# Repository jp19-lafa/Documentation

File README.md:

[![Contributors][contributors-shield]][contributors-url]
[![Forks][forks-shield]][forks-url]
[![Stargazers][stars-shield]][stars-url]
[![Issues][issues-shield]][issues-url]
[![MIT License][license-shield]][license-url]

<!-- PROJECT LOGO -->
<br />
<p align="center">

  <h3 align="center">DOCUMENTATION</h3>

  <p align="center">
    Wiki for farmlab
    <br />
    <a href="https://github.com/jp19-lafa/Documentation/wiki"><strong>Explore the docs »</strong></a>
    <br />
    <br />
    <a href="https://github.com/jp19-lafa/Documentation/issues">Report Bug</a>
    ·
    <a href="https://github.com/jp19-lafa/Documentation/issues">Request Feature</a>
  </p>
</p>

<!-- TABLE OF CONTENTS -->
## Table of Contents

- [Table of Contents](#table-of-contents)
- [About The Project](#about-the-project)
- [Roadmap](#roadmap)
- [Contributing](#contributing)
- [License](#license)
- [Team](#team)

<!-- ABOUT THE PROJECT -->
## About The Project
FarmLab is a class project for Smart Systems & IoT 2019 @ AP Antwerp. FarmLab is an automated hydroponics farm that utilizes an array of sensor to make smart decisions an create the optimal growing environment. Multiple nodes can work together to create a big farm network.

The cultivation of these plants follow the 'hydroponics' technique. This means the plants are planted directly in water without any type of soil. They are fed by nutrients added to that water.

_For the full explination please refer to the [Wiki](https://github.com/jp19-lafa/Documentation/wiki)_

<!-- ROADMAP -->
## Roadmap

See the [open issues](https://github.com/jp19-lafa/Documentation/issues) for a list of proposed features (and known issues).

<!-- CONTRIBUTING -->
## Contributing

Contributions are what make the open source community such an amazing place to be learn, inspire, and create. Any contributions you make are **greatly appreciated**.

1. Fork the Project
2. Create your Feature Branch (`git checkout -b feature/AmazingFeature`)
3. Commit your Changes (`git commit -m 'Add some AmazingFeature'`)
4. Push to the Branch (`git push origin feature/AmazingFeature`)
5. Open a Pull Request

<!-- LICENSE -->
## License

Distributed under the MIT License. See `LICENSE` for more information.

<!-- Team -->
## Team

Meurs Michiel - michiel.meurs1@gmail.com
<br>
Meyers Tom - tom@odex.be
<br>
Van Hoof Jonas - Jonas.vanhoof@student.ap.be
<br>
Vinck Ben - <!-- TODO: add a e-mail of Vincks choosing-->
<br>
Willemsen Matthias - <!-- TODO: add a e-mail of Willemsen's choosing-->

Project Link: [https://github.com/jp19-lafa/Documentation](https://github.com/jp19-lafa/Documentation)

<!-- MARKDOWN LINKS & IMAGES -->
<!-- https://www.markdownguide.org/basic-syntax/#reference-style-links -->
[contributors-shield]: https://img.shields.io/github/contributors/jp19-lafa/Documentation.svg?style=flat-square
[contributors-url]: https://github.com/jp19-lafa/Documentation/graphs/contributors
[forks-shield]: https://img.shields.io/github/forks/jp19-lafa/Documentation.svg?style=flat-square
[forks-url]: https://github.com/jp19-lafa/Documentation/network/members
[stars-shield]: https://img.shields.io/github/stars/jp19-lafa/Documentation.svg?style=flat-square
[stars-url]: https://github.com/jp19-lafa/Documentation/stargazers
[issues-shield]: https://img.shields.io/github/issues/jp19-lafa/Documentation.svg?style=flat-square
[issues-url]: https://github.com/jp19-lafa/Documentation/issues
[license-shield]: https://img.shields.io/github/license/jp19-lafa/Documentation.svg?style=flat-square
[license-url]: https://github.com/jp19-lafa/Documentation/blob/master/LICENSE.txt
[product-screenshot]: https://raw.githubusercontent.com/jp19-lafa/Documentation/master/images/branding/plant_transparent.svg

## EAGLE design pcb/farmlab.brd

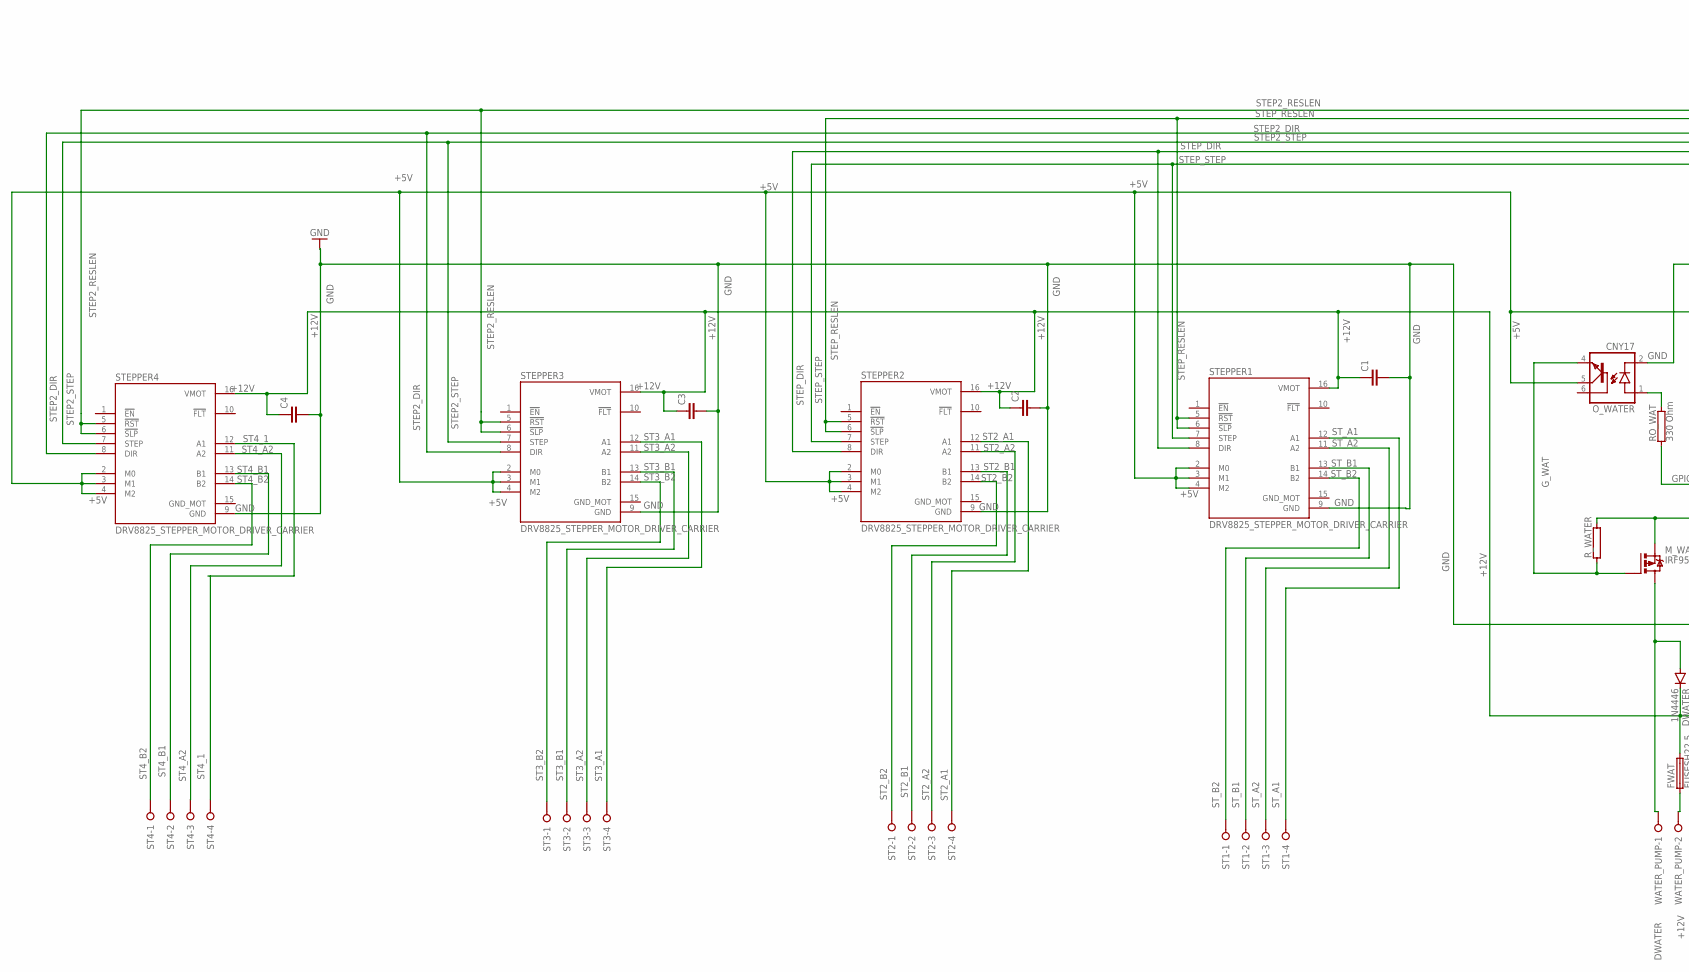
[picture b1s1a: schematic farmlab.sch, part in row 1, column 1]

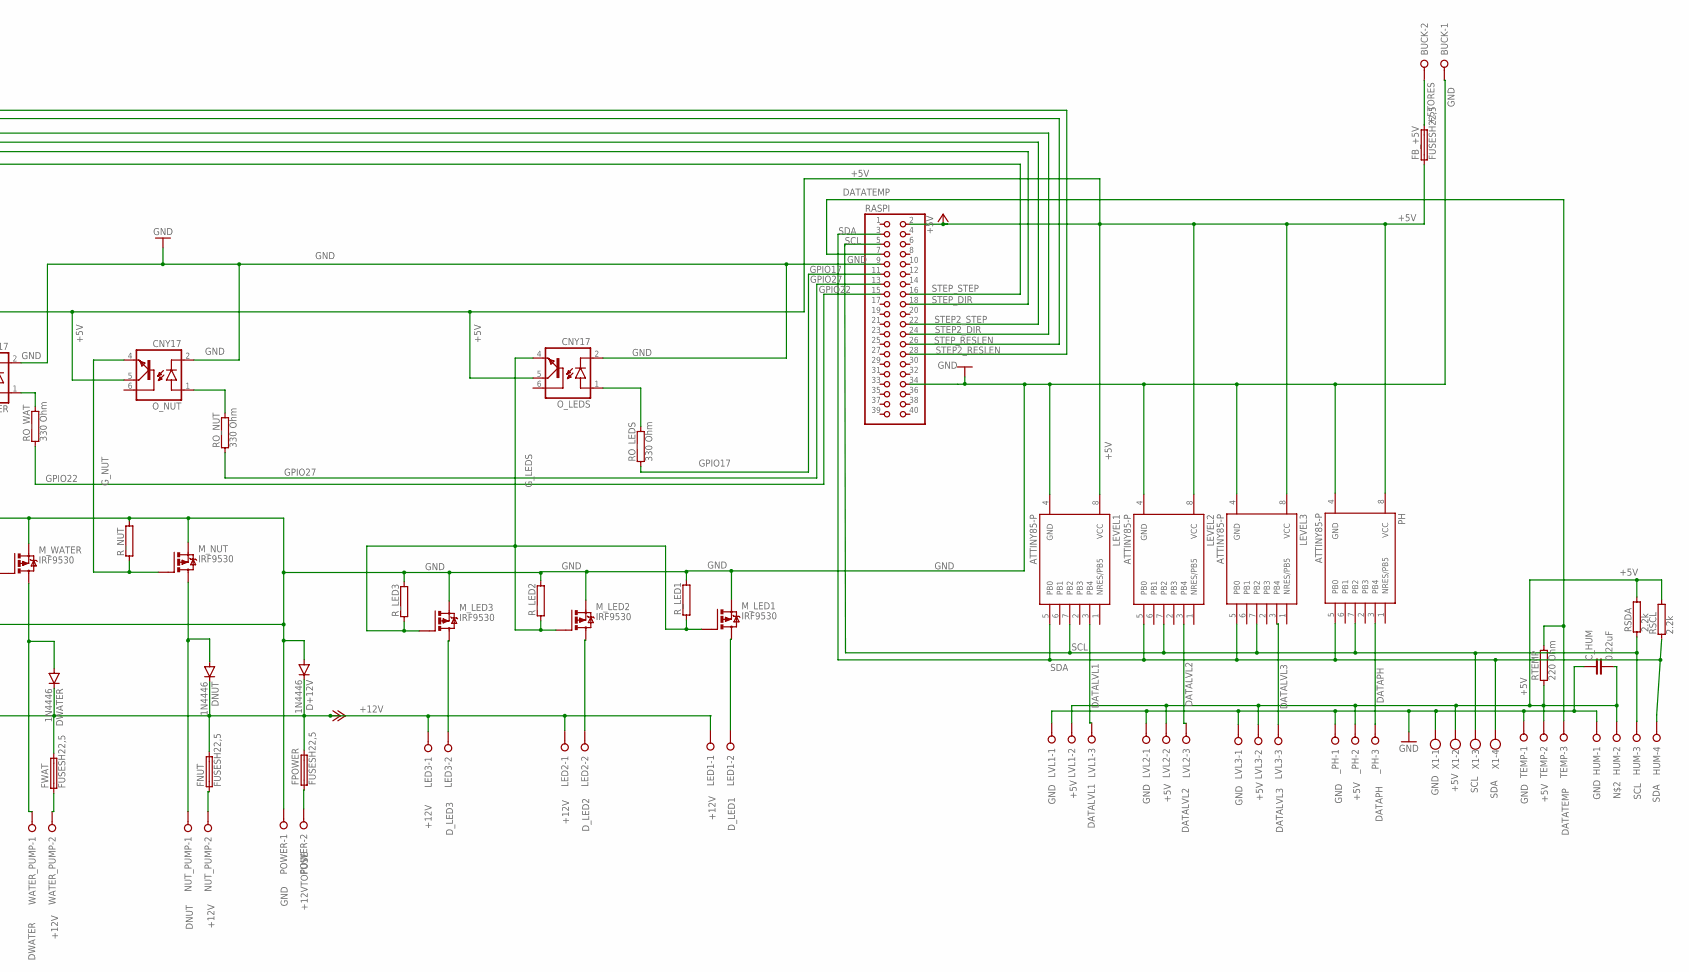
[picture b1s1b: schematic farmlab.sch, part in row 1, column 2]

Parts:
BUCK: W237-02P; W237-132
C1, C2, C3, C4: C2.5/6; C2.5-6
C_HUM: 0.22uF; C2.5-6
D+12V: 1N4446; DO35-10
DNUT: 1N4446; DO35-10
DWATER: 1N4446; DO35-10
FB_+5V: FUSESH22,5; SH22,5
FNUT: FUSESH22,5; SH22,5
FPOWER: FUSESH22,5; SH22,5
FWAT: FUSESH22,5; SH22,5
HUM: W237-04P; W237-4P
LED1, LED2, LED3: W237-02P; W237-132
LEVEL1, LEVEL2, LEVEL3: ATTINY85-P; PDIP08_300MIL
LVL1, LVL2, LVL3: W237-3E
M_LED1, M_LED2, M_LED3: IRF9530; TO220BV
M_NUT: IRF9530; TO220BV
M_WATER: IRF9530; TO220BV
NUT_PUMP: W237-02P; W237-132
O_LEDS: CNY17; DIL06
O_NUT: CNY17; DIL06
O_WATER: CNY17; DIL06
PH: ATTINY85-P; PDIP08_300MIL
POWER: W237-02P; W237-132
RASPI: PINHD-2X20; 2X20
RO_LEDS: 330 Ohm; AC03
RO_NUT: 330 Ohm; AC03
RO_WAT: 330 Ohm; AC03
RSCL: 2.2k; AC03
RSDA: 2.2k; AC03
RTEMP: 220 Ohm; AC03
R_LED1, R_LED2, R_LED3: RAC03; AC03
R_NUT: RAC03; AC03
R_WATER: RAC03; AC03
ST1, ST2, ST3, ST4: W237-04P; W237-4P
STEPPER1, STEPPER2, STEPPER3, STEPPER4: DRV8825_STEPPER_MOTOR_DRIVER_CARRIER; IC_DRV8825_STEPPER_MOTOR_DRIVER_CARRIER
TEMP: W237-3E
WATER_PUMP: W237-02P; W237-132
X1: W237-4
_PH: W237-3E

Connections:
+5TORES: BUCK.2, FB_+5V.2
+5V: C_HUM.2, FB_+5V.1, LEVEL1.8 (VCC), LEVEL2.8 (VCC), LEVEL3.8 (VCC), LVL1.2, LVL2.2, LVL3.2, O_LEDS.5 (COL), O_NUT.5 (COL), O_WATER.5 (COL), PH.8 (VCC), RASPI.2, RSCL.2, RSDA.2, RTEMP.1, STEPPER1.2 (M0), STEPPER1.3 (M1), STEPPER1.4 (M2), STEPPER2.2 (M0), STEPPER2.3 (M1), STEPPER2.4 (M2), STEPPER3.2 (M0), STEPPER3.3 (M1), STEPPER3.4 (M2), STEPPER4.2 (M0), STEPPER4.3 (M1), STEPPER4.4 (M2), TEMP.2, X1.2, _PH.2
+12V: C1.1, C2.1, C3.1, C4.1, D+12V.C, DNUT.C, DWATER.C, FNUT.2, FPOWER.2, FWAT.2, LED1.1, LED2.1, LED3.1, STEPPER1.16 (VMOT), STEPPER2.16 (VMOT), STEPPER3.16 (VMOT), STEPPER4.16 (VMOT)
+12VTOFUSE: FPOWER.1, POWER.2
DATALVL1: LEVEL1.3 (PB4), LVL1.3
DATALVL2: LEVEL2.3 (PB4), LVL2.3
DATALVL3: LEVEL3.3 (PB4), LVL3.3
DATAPH: PH.3 (PB4), _PH.3
DATATEMP: RASPI.7, RTEMP.2, TEMP.3
DNUT: DNUT.A, M_NUT.D, NUT_PUMP.1
DWATER: DWATER.A, M_WATER.D, WATER_PUMP.1
D_LED1: LED1.2, M_LED1.D
D_LED2: LED2.2, M_LED2.D
D_LED3: LED3.2, M_LED3.D
GND: BUCK.1, C1.2, C2.2, C3.2, C4.2, C_HUM.1, D+12V.A, HUM.1, LEVEL1.4 (GND), LEVEL2.4 (GND), LEVEL3.4 (GND), LVL1.1, LVL2.1, LVL3.1, M_LED1.S, M_LED2.S, M_LED3.S, M_NUT.S, M_WATER.S, O_LEDS.2 (C), O_NUT.2 (C), O_WATER.2 (C), PH.4 (GND), POWER.1, RASPI.9, RASPI.34, R_LED1.2, R_LED2.2, R_LED3.2, R_NUT.2, R_WATER.2, STEPPER1.9 (GND), STEPPER2.9 (GND), STEPPER3.9 (GND), STEPPER4.9 (GND), TEMP.1, X1.1, _PH.1
GND_MOT: STEPPER1.15 (GND_MOT), STEPPER2.15 (GND_MOT), STEPPER3.15 (GND_MOT), STEPPER4.15 (GND_MOT)
GPIO17: RASPI.11, RO_LEDS.1
GPIO22: RASPI.15, RO_WAT.1
GPIO27: RASPI.13, RO_NUT.1
G_LEDS: M_LED1.G, M_LED2.G, M_LED3.G, O_LEDS.4 (EMI), R_LED1.1, R_LED2.1, R_LED3.1
G_NUT: M_NUT.G, O_NUT.4 (EMI), R_NUT.1
G_WAT: M_WATER.G, O_WATER.4 (EMI), R_WATER.1
unnamed: O_WATER.1 (A), RO_WAT.2
unnamed: O_NUT.1 (A), RO_NUT.2
unnamed: O_LEDS.1 (A), RO_LEDS.2
unnamed: FNUT.1, NUT_PUMP.2
unnamed: FWAT.1, WATER_PUMP.2
SCL: HUM.3, LEVEL1.7 (PB2), LEVEL2.7 (PB2), LEVEL3.7 (PB2), PH.7 (PB2), RASPI.5, RSDA.1, X1.3
SDA: HUM.4, LEVEL1.5 (PB0), LEVEL2.5 (PB0), LEVEL3.5 (PB0), PH.5 (PB0), RASPI.3, RSCL.1, X1.4
ST2_A1: ST2.4, STEPPER2.12 (A1)
ST2_A2: ST2.3, STEPPER2.11 (A2)
ST2_B1: ST2.2, STEPPER2.13 (B1)
ST2_B2: ST2.1, STEPPER2.14 (B2)
ST3_A1: ST3.4, STEPPER3.12 (A1)
ST3_A2: ST3.3, STEPPER3.11 (A2)
ST3_B1: ST3.2, STEPPER3.13 (B1)
ST3_B2: ST3.1, STEPPER3.14 (B2)
ST4_1: ST4.4, STEPPER4.12 (A1)
ST4_A2: ST4.3, STEPPER4.11 (A2)
ST4_B1: ST4.2, STEPPER4.13 (B1)
ST4_B2: ST4.1, STEPPER4.14 (B2)
STEP2_DIR: RASPI.24, STEPPER3.8 (DIR), STEPPER4.8 (DIR)
STEP2_RESLEN: RASPI.28, STEPPER3.5 (!RST), STEPPER3.6 (!SLP), STEPPER4.5 (!RST), STEPPER4.6 (!SLP)
STEP2_STEP: RASPI.22, STEPPER3.7 (STEP), STEPPER4.7 (STEP)
STEP_DIR: RASPI.18, STEPPER1.8 (DIR), STEPPER2.8 (DIR)
STEP_RESLEN: RASPI.26, STEPPER1.5 (!RST), STEPPER1.6 (!SLP), STEPPER2.5 (!RST), STEPPER2.6 (!SLP)
STEP_STEP: RASPI.16, STEPPER1.7 (STEP), STEPPER2.7 (STEP)
ST_A1: ST1.4, STEPPER1.12 (A1)
ST_A2: ST1.3, STEPPER1.11 (A2)
ST_B1: ST1.2, STEPPER1.13 (B1)
ST_B2: ST1.1, STEPPER1.14 (B2)

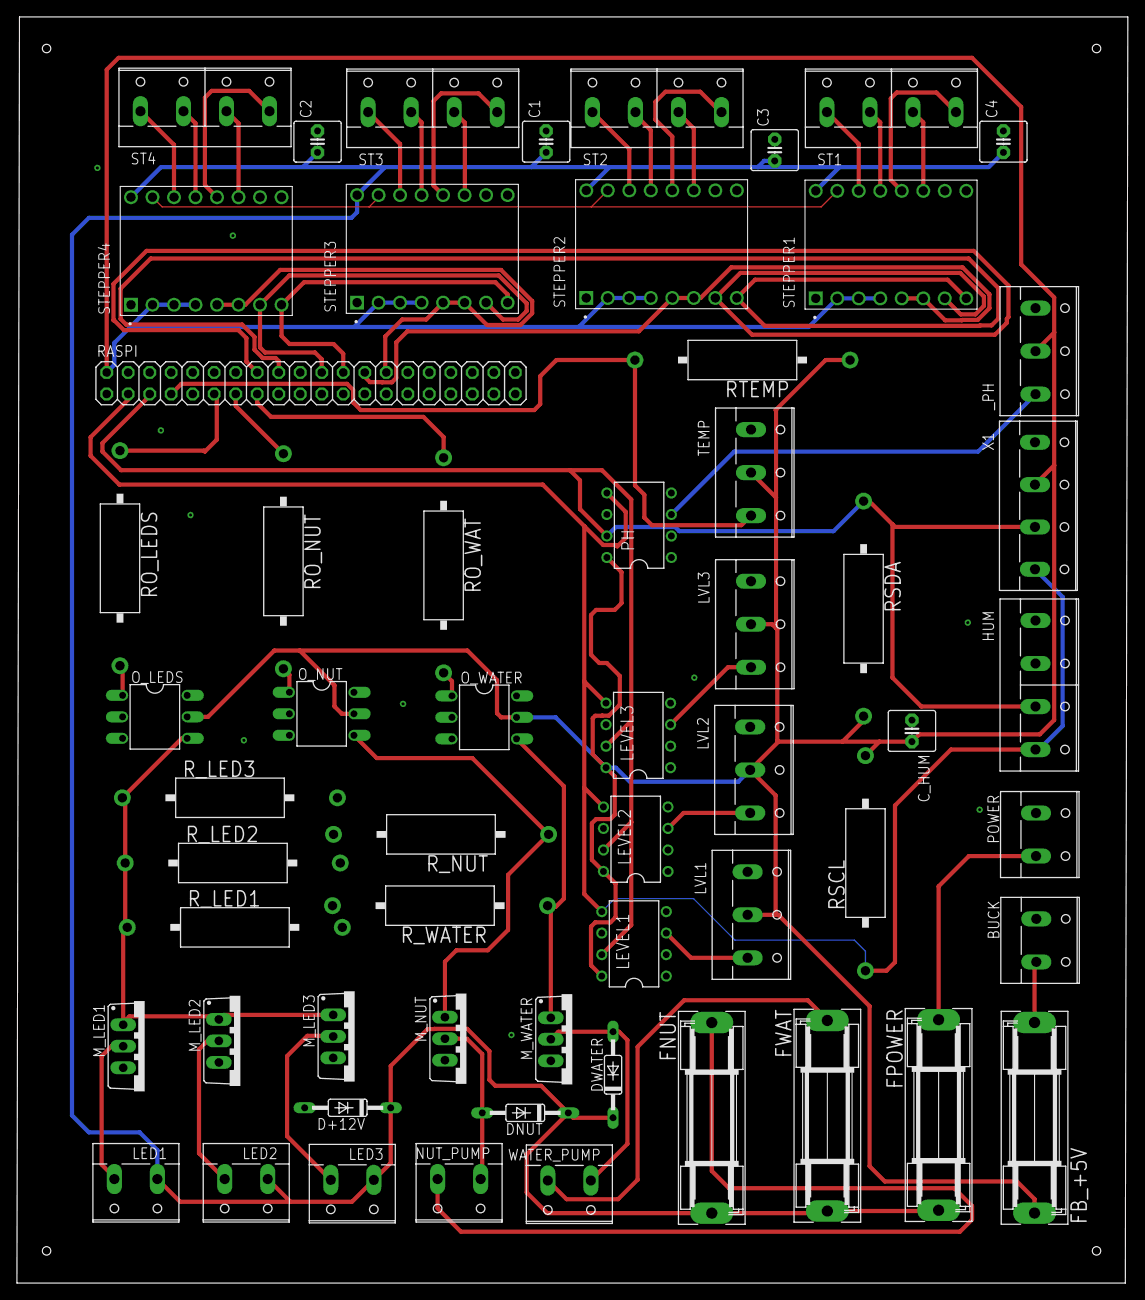
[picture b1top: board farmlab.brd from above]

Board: 2 copper layers, 131.2 x 149.5 mm, 58 parts (0 on the bottom side), 51 nets.

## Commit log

2019-09-16 Added branding usable as a reference in the wiki
2019-09-16 Initial readme
    The initial readme has been created.
    However we still need to fill in the e-mails of all members of the team
    Perhaps even there roles. However this is not so relevant
2019-09-16 Set link to a relative path
2019-09-16 Added branding to readme
2019-09-16 Scaled image
2019-09-16 Altered table of content
2019-09-16 [ImgBot] Optimize images
    /images/branding/plant_transparent.png -- 16.03kb -> 13.51kb (15.72%)
2019-09-16 Clang formater for c/c++
    Added a basic style formatter for c based languages
2019-09-16 Formatter for c/c++ and javascript
2019-09-16 Added prettierrc
    format typescript
2019-09-16 Added specifications of the sensors + images
2019-09-16 Update issue templates
2019-09-17 Moved images to Images/Branding All the images that I used in my document Sensors.md where moved to the path Images/Branding.
2019-09-17 Added coding rules to Sensors.md Corrected the style of the document to the coding ruls for a markdown document.
2019-09-19 Moved sensor images Added directory /images/sensors. Moved the sensor images from images/branding to /images/sensors.
2019-09-19 Updated Sensors.md Centered the sensor images and changed the image links. Added the level sensor analysis to the document.
2019-09-19 Deleted Sensors.md Added the content of Sensors.md to the wiki => Analysis => Sensors. Deleted Sensors.md to clean the work tree.
2019-09-19 [ImgBot] Optimize images
    *Total -- 147.66kb -> 99.32kb (32.73%)
    /images/sensors/Ph_scale.png -- 58.96kb -> 23.44kb (60.24%)
    /images/sensors/Schematic_HIHI6030.png -- 10.53kb -> 8.33kb (20.85%)
    /images/sensors/Pinout_HIH6030.png -- 73.60kb -> 63.47kb (13.76%)
    /images/sensors/Pinout_DS18B20.png -- 4.57kb -> 4.08kb (10.81%)
2019-09-19 Added argumentations Made a document that says while farmlab.
2019-09-19 Deleted argumentation.md Deleted the file where I created the argumentation wiki.
2019-09-20 Create LICENSE
2019-09-20 Fixed Layout prefixes
    Changed the table of contents prefixes to follow the markdown guide in the wiki
2019-09-20 Added images and actuator analysis.md Added a document that analyses all the actuators use in Farmlab. All images used in actuators.md are added in images/actuators.
2019-09-20 Updated actuators.md Added the stepper motor driver to the analysis.
2019-09-20 Added My emaill
2019-09-20 Added Jonas' emaill
2019-09-23 Added images for analysis
    These images are used in the wiki page for the analysis
2019-09-23 Created folder design
    I moved the .drawio and .mup files that were used to create some diagrams to a new folder called designs.
2019-09-23 [ImgBot] Optimize images
    *Total -- 3,223.91kb -> 1,994.49kb (38.13%)
    /images/flowcharts/ATTiny_flowchart.png -- 44.20kb -> 13.96kb (68.41%)
    /images/general/hardware_blockdiagram.png -- 27.52kb -> 13.25kb (51.85%)
    /images/web/erd_database.png -- 98.04kb -> 48.95kb (50.07%)
    /images/web/node_unreliable.png -- 15.34kb -> 8.29kb (45.95%)
    /images/general/state_diagram.png -- 23.23kb -> 13.03kb (43.91%)
2019-10-10 Added PCB relaed images Added in folder images/PCB/ Schematic.png and Board.png
2019-10-10 Added Manufactered PCB board image Changed folder name images/PCB to images/pcb. 3D model of the future PCB board added in images/pcb/
2019-10-11 [ImgBot] Optimize images
    *Total -- 143.30kb -> 101.90kb (28.89%)
    /images/pcb/Board.png -- 31.04kb -> 15.26kb (50.84%)
    /images/pcb/Schematic.png -- 16.80kb -> 9.44kb (43.8%)
    /images/pcb/Manufactered_Board.png -- 93.47kb -> 75.50kb (19.23%)
    /images/branding/plant_transparent.svg -- 1.99kb -> 1.70kb (14.17%)
2020-03-11 Added pcb scheme
    - added the most recent pcb schema from jp19-lafa
